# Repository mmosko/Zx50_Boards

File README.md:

# Zx50 Project Architecture Context

## Overview

The Zx50 is a custom 8-slot, passive backplane Z80 computer. It uses a "Shadow Bus" architecture where a Raspberry Pi Pico can take over the bus via DMA (~BUSRQ / ~BUSAK) to load RAM, debug, and monitor the system.

## Core Rules & Hardware

* Backplane: 8 slots. Fully terminated with 10K SIP pull-up resistors on Address, Data, and Control lines. Includes an ~IEI/~IEO interrupt daisy chain and heavy bulk capacitance (1000µF).

* CPU: Z80 running at 8 to 10 MHz.

* Clock System: A dedicated Clock Mezzanine board that generates a 40 MHz Master Clock (MCLK) for the Pi Picos, and uses a 74HC393 to divide it down to a 10 MHz ZCLK for the Z80. It uses an async-request latch system (1G79, 1G08, 1G32) to perfectly sync the CPU clock stopping/stepping with the Pi Pico's requests, ensuring no runt pulses.

* Logic Families: * 74AHCT (specifically 74AHCT244 and 74AHCT245) are used for bus transceivers to provide the strong ±8mA current needed to drive the backplane.

* Standard 74HC / 74AHC logic is used for local onboard glue logic.

* System Reset: Handled by an MCP1316M-46LE/OT Open-Drain Supervisor IC on the CPU card. It provides a ~200ms reset timeout to allow the backplane capacitors to charge and the Pi Pico bootloaders to initialize before the Z80 wakes up.

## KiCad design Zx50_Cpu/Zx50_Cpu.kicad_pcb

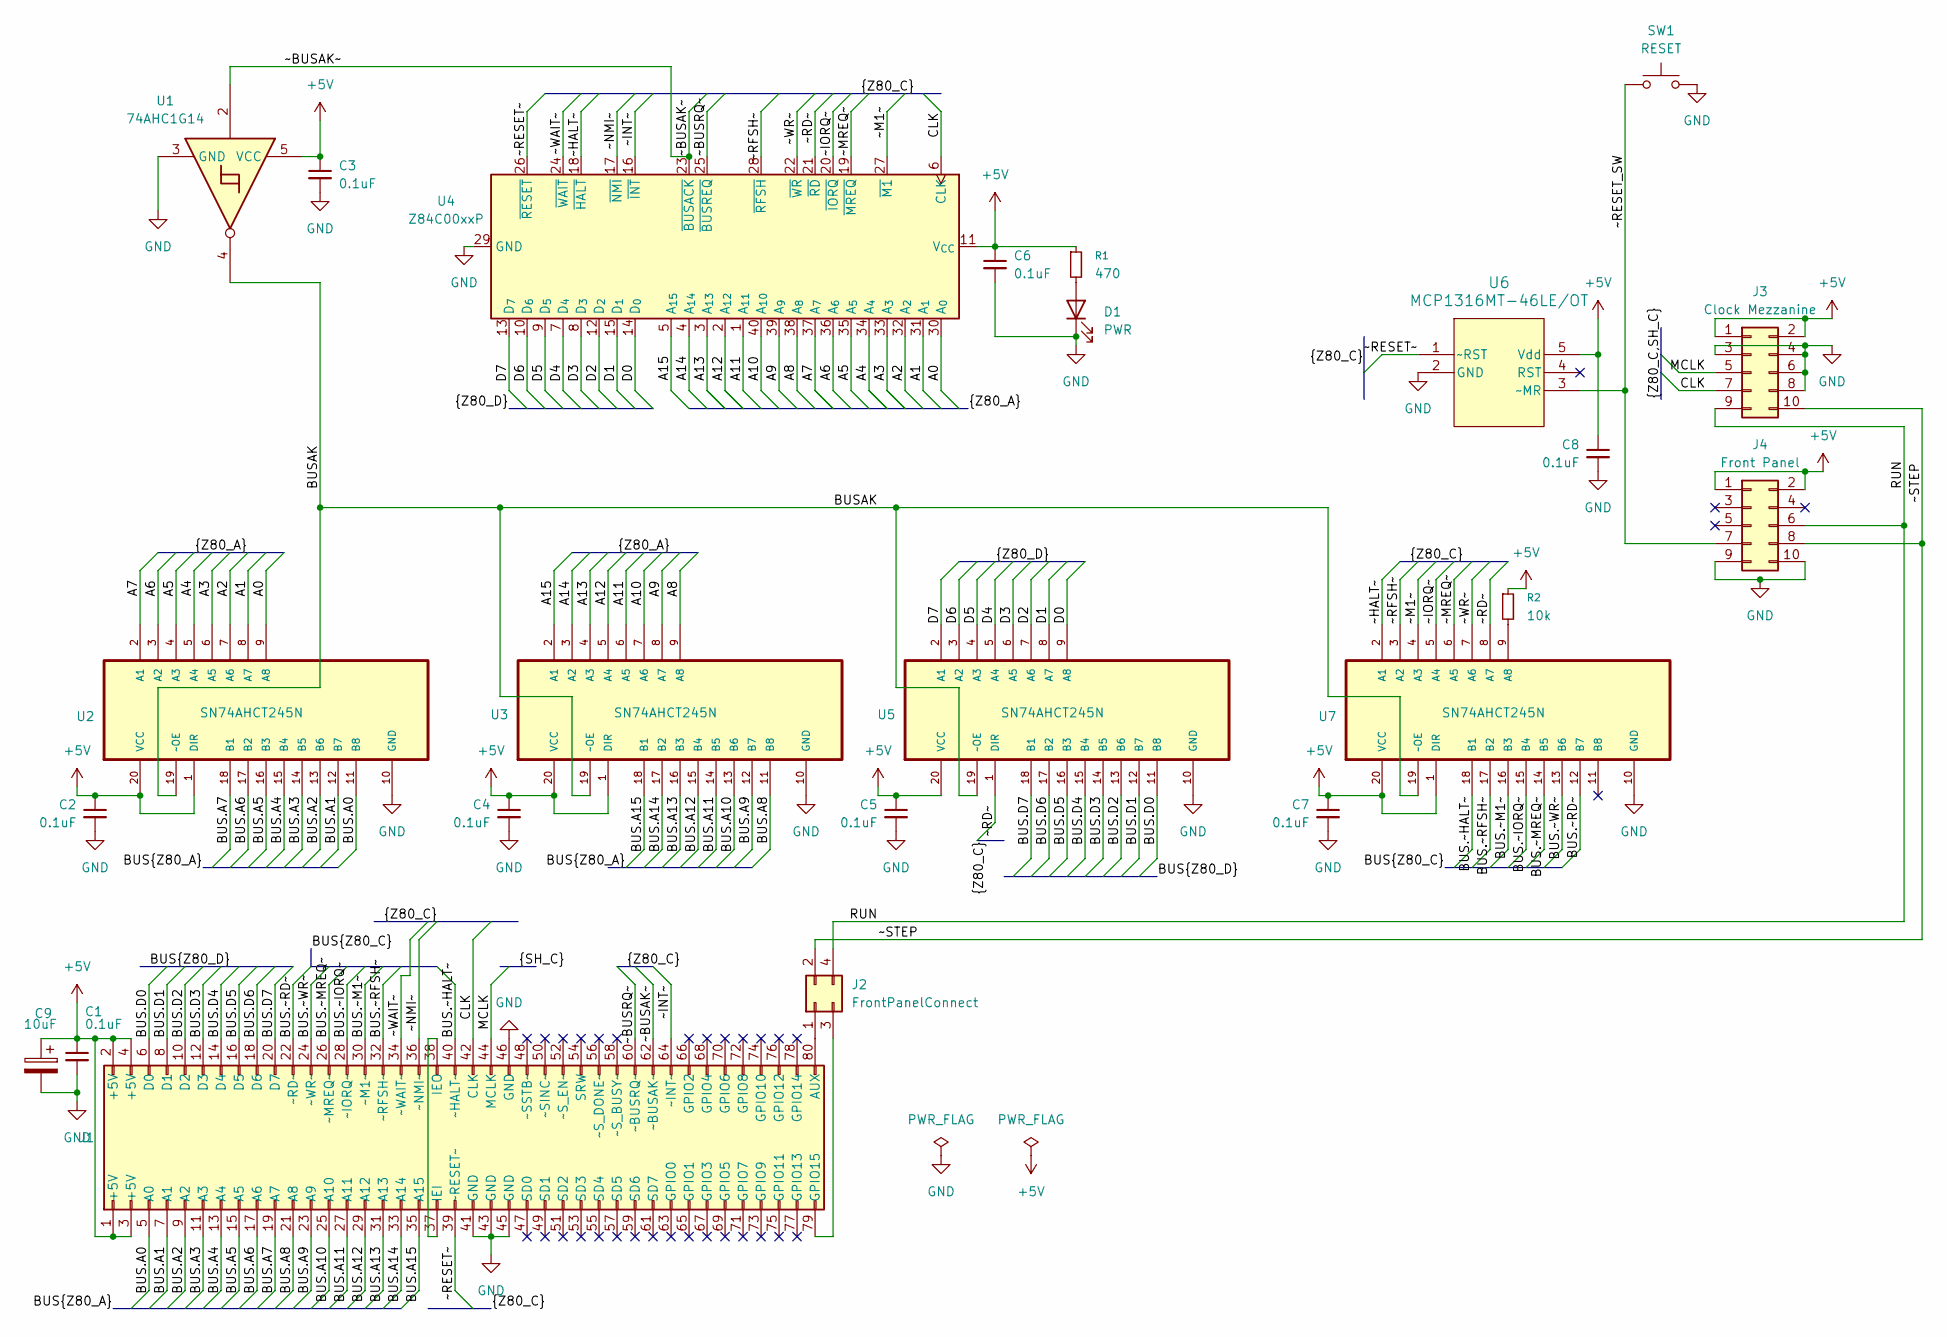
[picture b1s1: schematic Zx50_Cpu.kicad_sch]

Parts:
C1, C2, C3, C4, C5, C6, C7, C8: 0.1uF; C_Disc_D5.0mm_W2.5mm_P5.00mm; DigiKey_PN BC1101CT-ND
C9: 10uF; CP_Radial_Tantal_D5.0mm_P2.50mm; DigiKey_PN 399-1418-ND
D1: PWR; LED_D5.0mm
J1: Zx50_EdgeConnector; PinSocket_2x40_P2.54mm_Vertical_Oval; DigiKey_PN A34273-40-ND
J2: FrontPanelConnect; PinSocket_2x02_P2.54mm_Vertical; DigiKey_PN S1012E-02-ND
J3: Clock Mezzanine; PinSocket_2x05_P2.54mm_Horizontal; DigiKey_PN 732-2098-ND
J4: Front Panel; IDC-Header_2x05_P2.54mm_Horizontal_Edge; DigiKey_PN 732-2098-ND
R1: 470; R_Axial_DIN0207_L6.3mm_D2.5mm_P10.16mm_Horizontal
R2: 10k; R_Axial_DIN0207_L6.3mm_D2.5mm_P5.08mm_Vertical
SW1: RESET; SW_PUSH_6mm_H7.3mm; DigiKey_PN SW402-ND
U1: 74AHC1G14; SOT-23-5_HandSoldering; DigiKey_PN 296-1088-1-ND
U2, U3, U5: SN74AHCT245N; DIP-20_W7.62mm_Socket; MPN SN74AHCT245N; Digikey_PN 296-1476-5-ND
U4: Z84C00xxP; DIP-40_W15.24mm
U6: MCP1316MT-46LE/OT; SOT-23-5_MC_MCH; DigiKey_PN MCP1318MT-46LE/OTCT-ND
U7: SN74AHCT245N; DIP-20_W7.62mm_Socket; MPN SN74AHCT245N; DigiKey_PN 296-1476-5-ND

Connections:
+5V: C1.1, C2.1, C3.1, C4.1, C5.1, C6.1, C7.1, C8.1, C9.1, J1.1 (+5V), J1.2 (+5V), J1.3 (+5V), J1.4 (+5V), J3.1, J3.2, J4.1, J4.2, R1.1, R2.1, U1.5 (VCC), U2.1 (DIR), U2.20 (VCC), U3.1 (DIR), U3.20 (VCC), U4.11 (V_{CC}), U5.20 (VCC), U6.5 (Vdd), U7.1 (DIR), U7.20 (VCC)
/A0: U2.9 (A8), U4.30 (A_{0})
/A1: U2.8 (A7), U4.31 (A_{1})
/A2: U2.7 (A6), U4.32 (A_{2})
/A3: U2.6 (A5), U4.33 (A_{3})
/A4: U2.5 (A4), U4.34 (A_{4})
/A5: U2.4 (A3), U4.35 (A_{5})
/A6: U2.3 (A2), U4.36 (A_{6})
/A7: U2.2 (A1), U4.37 (A_{7})
/A8: U3.9 (A8), U4.38 (A_{8})
/A9: U3.8 (A7), U4.39 (A_{9})
/A10: U3.7 (A6), U4.40 (A_{10})
/A11: U3.6 (A5), U4.1 (A_{11})
/A12: U3.5 (A4), U4.2 (A_{12})
/A13: U3.4 (A3), U4.3 (A_{13})
/A14: U3.3 (A2), U4.4 (A_{14})
/A15: U3.2 (A1), U4.5 (A_{15})
/BUS.A0: J1.5 (A0), U2.11 (B8)
/BUS.A1: J1.7 (A1), U2.12 (B7)
/BUS.A2: J1.9 (A2), U2.13 (B6)
/BUS.A3: J1.11 (A3), U2.14 (B5)
/BUS.A4: J1.13 (A4), U2.15 (B4)
/BUS.A5: J1.15 (A5), U2.16 (B3)
/BUS.A6: J1.17 (A6), U2.17 (B2)
/BUS.A7: J1.19 (A7), U2.18 (B1)
/BUS.A8: J1.21 (A8), U3.11 (B8)
/BUS.A9: J1.23 (A9), U3.12 (B7)
/BUS.A10: J1.25 (A10), U3.13 (B6)
/BUS.A11: J1.27 (A11), U3.14 (B5)
/BUS.A12: J1.29 (A12), U3.15 (B4)
/BUS.A13: J1.31 (A13), U3.16 (B3)
/BUS.A14: J1.33 (A14), U3.17 (B2)
/BUS.A15: J1.35 (A15), U3.18 (B1)
/BUS.D0: J1.6 (D0), U5.11 (B8)
/BUS.D1: J1.8 (D1), U5.12 (B7)
/BUS.D2: J1.10 (D2), U5.13 (B6)
/BUS.D3: J1.12 (D3), U5.14 (B5)
/BUS.D4: J1.14 (D4), U5.15 (B4)
/BUS.D5: J1.16 (D5), U5.16 (B3)
/BUS.D6: J1.18 (D6), U5.17 (B2)
/BUS.D7: J1.20 (D7), U5.18 (B1)
/BUS.~HALT~: J1.40 (~HALT~), U7.18 (B1)
/BUS.~IORQ~: J1.28 (~IORQ~), U7.15 (B4)
/BUS.~M1~: J1.30 (~M1~), U7.16 (B3)
/BUS.~MREQ~: J1.26 (~MREQ~), U7.14 (B5)
/BUS.~RD~: J1.22 (~RD~), U7.12 (B7)
/BUS.~RFSH~: J1.32 (~RFSH~), U7.17 (B2)
/BUS.~WR~: J1.24 (~WR~), U7.13 (B6)
/BUSAK: U1.4, U2.19 (~OE), U3.19 (~OE), U5.19 (~OE), U7.19 (~OE)
/CLK: J1.42 (CLK), J3.7, U4.6 (CLK)
/D0: U4.14 (D_{0}), U5.9 (A8)
/D1: U4.15 (D_{1}), U5.8 (A7)
/D2: U4.12 (D_{2}), U5.7 (A6)
/D3: U4.8 (D_{3}), U5.6 (A5)
/D4: U4.7 (D_{4}), U5.5 (A4)
/D5: U4.9 (D_{5}), U5.4 (A3)
/D6: U4.10 (D_{6}), U5.3 (A2)
/D7: U4.13 (D_{7}), U5.2 (A1)
/MCLK: J1.44 (MCLK), J3.5
/RUN: J2.4, J3.9, J4.6
/~BUSAK~: J1.62 (~BUSAK~), U1.2, U4.23 (~BUSACK)
/~BUSRQ~: J1.60 (~BUSRQ~), U4.25 (~BUSREQ)
/~HALT~: U4.18 (~HALT), U7.2 (A1)
/~INT~: J1.64 (~INT~), U4.16 (~INT)
/~IORQ~: U4.20 (~IORQ), U7.5 (A4)
/~M1~: U4.27 (~M1), U7.4 (A3)
/~MREQ~: U4.19 (~MREQ), U7.6 (A5)
/~NMI~: J1.36 (~NMI~), U4.17 (~NMI)
/~RD~: U4.21 (~RD), U5.1 (DIR), U7.8 (A7)
/~RESET_SW: J4.7, SW1.1, U6.3 (~MR)
/~RESET~: J1.39 (~RESET~), U4.26 (~RESET), U6.1 (~RST)
/~RFSH~: U4.28 (~RFSH), U7.3 (A2)
/~STEP: J2.2, J3.10, J4.8
/~WAIT~: J1.34 (~WAIT~), U4.24 (~WAIT)
/~WR~: U4.22 (~WR), U7.7 (A6)
GND: C1.2, C2.2, C3.2, C4.2, C5.2, C6.2, C7.2, C8.2, C9.2, D1.1 (K), J1.41 (GND), J1.43 (GND), J1.45 (GND), J1.46 (GND), J3.3, J3.4, J3.6, J3.8, J4.9, J4.10, SW1.2, U1.3 (GND), U2.10 (GND), U3.10 (GND), U4.29 (GND), U5.10 (GND), U6.2 (GND), U7.10 (GND)
unnamed: D1.2 (A), R1.2
unnamed: J1.80 (AUX), J2.1
unnamed: J1.79 (GPIO15), J2.3
unnamed: J1.37 (IEI), J1.38 (IEO)
unnamed: R2.2, U7.9 (A8)

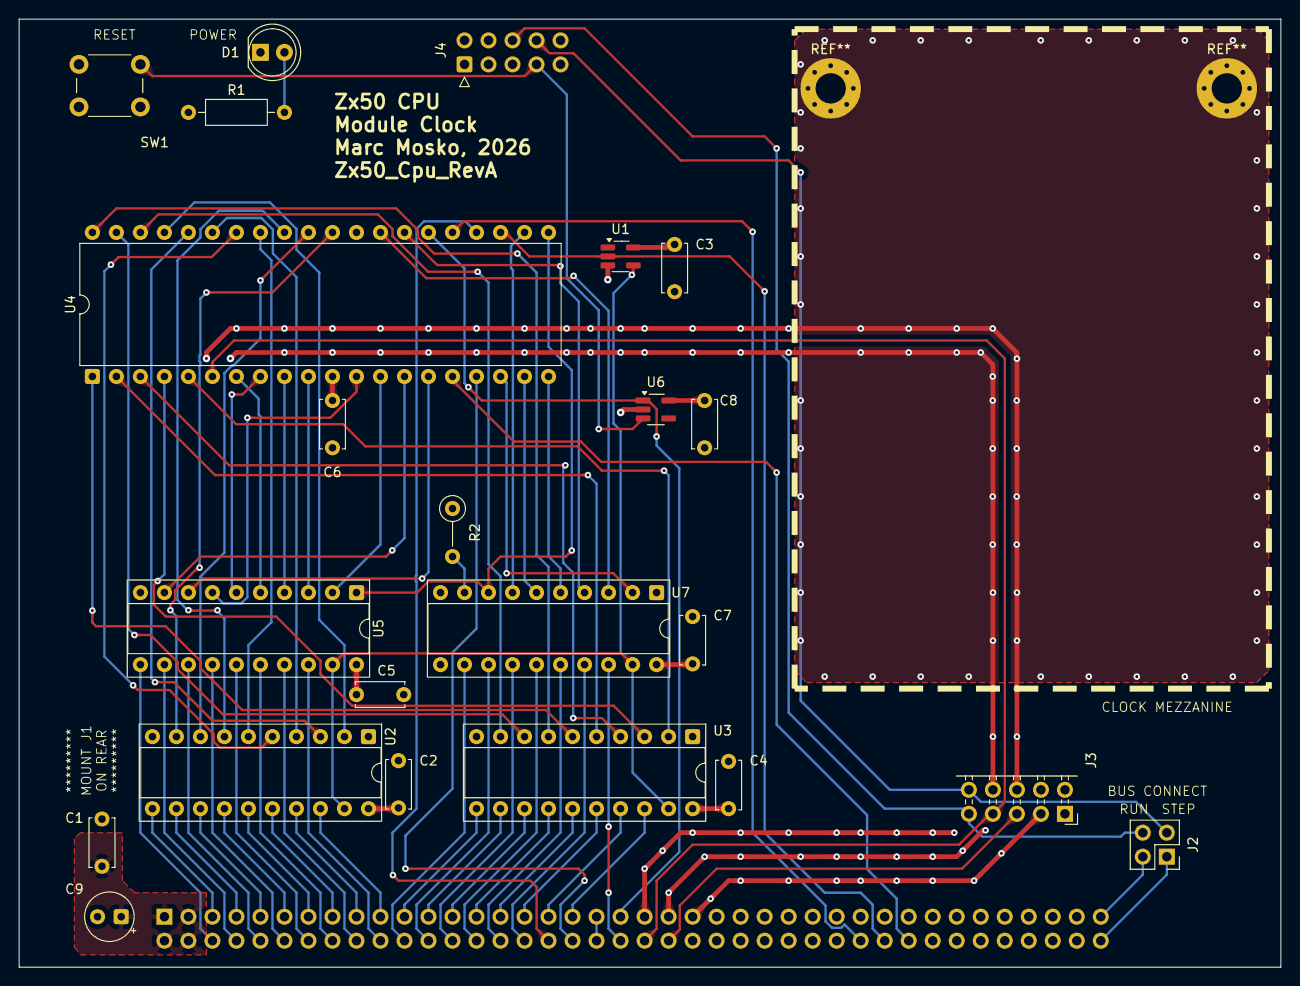
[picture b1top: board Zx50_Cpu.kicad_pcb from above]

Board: 4 copper layers, 133.5 x 100.3 mm, 24 parts (1 on the bottom side), 81 nets.

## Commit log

2026-03-09 Memory and rom cd
2026-03-11 RevA.6 as sent to fab.
2026-03-13 move files in big reorg
2026-03-13 unify kicad for zx50 in one repo
2026-03-14 documentation updates
2026-03-14 add front panel description
2026-03-14 before routing
2026-03-14 add csv files.
2026-03-14 add mounting holes
2026-03-15 finish up cpu card, begin on serial card.
